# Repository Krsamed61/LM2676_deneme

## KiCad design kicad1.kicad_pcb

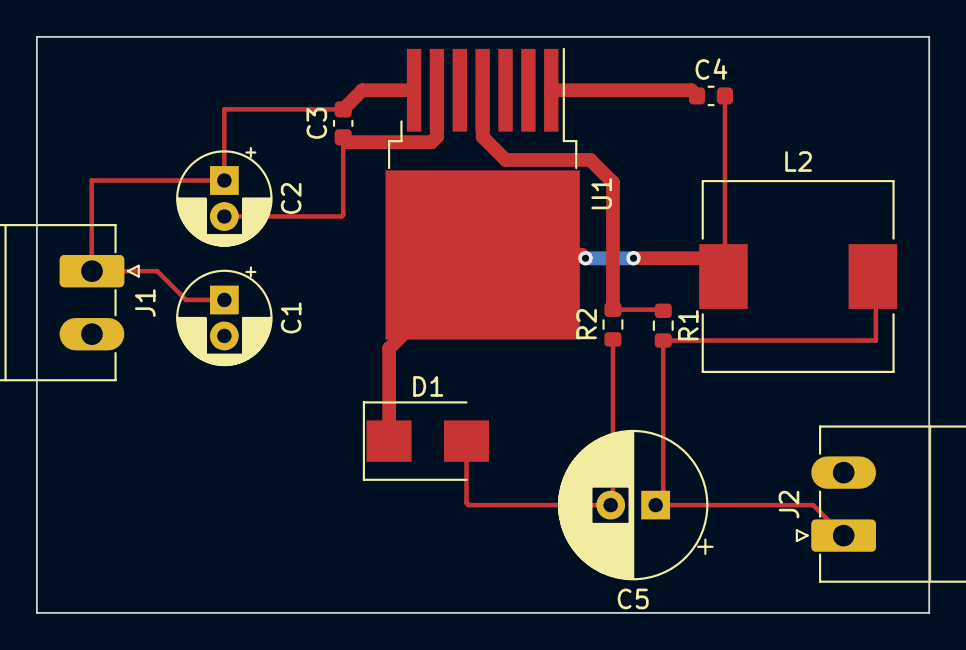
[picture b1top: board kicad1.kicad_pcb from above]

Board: 2 copper layers, 49.6 x 32.0 mm, 12 parts (0 on the bottom side), 6 nets.

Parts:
C1, C2: 47uF; CP_Radial_D5.0mm_P2.00mm
C3: 470nf; C_0603_1608Metric
C4: 1nf; C_0603_1608Metric
C5: 330uF; CP_Radial_D8.0mm_P2.50mm
D1: SS14; D_SMB
J1: Vin; PhoenixContact_MC_1,5_2-G-3.5_1x02_P3.50mm_Horizontal
J2: Vout; PhoenixContact_MC_1,5_2-G-3.5_1x02_P3.50mm_Horizontal
L2: 33u; L_10.4x10.4_H4.8
R1, R2: TBD; R_0603_1608Metric
U1: LM2676-5v; TO-263-7_TabPin8

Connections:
GND: C1.2, C2.2, C3.1, C5.2, D1.2 (A), J1.2, J2.2, R2.1, U1.6 (GND)
unnamed: C1.1, C2.1, C3.2, J1.1, U1.7 (VIN)
unnamed: C4.1, U1.1 (CB)
unnamed: C4.2, D1.1 (K), L2.1, U1.8 (VSW)
unnamed: C5.1, J2.1, L2.2, R1.2
unnamed: R1.1, R2.2, U1.4 (FB)
